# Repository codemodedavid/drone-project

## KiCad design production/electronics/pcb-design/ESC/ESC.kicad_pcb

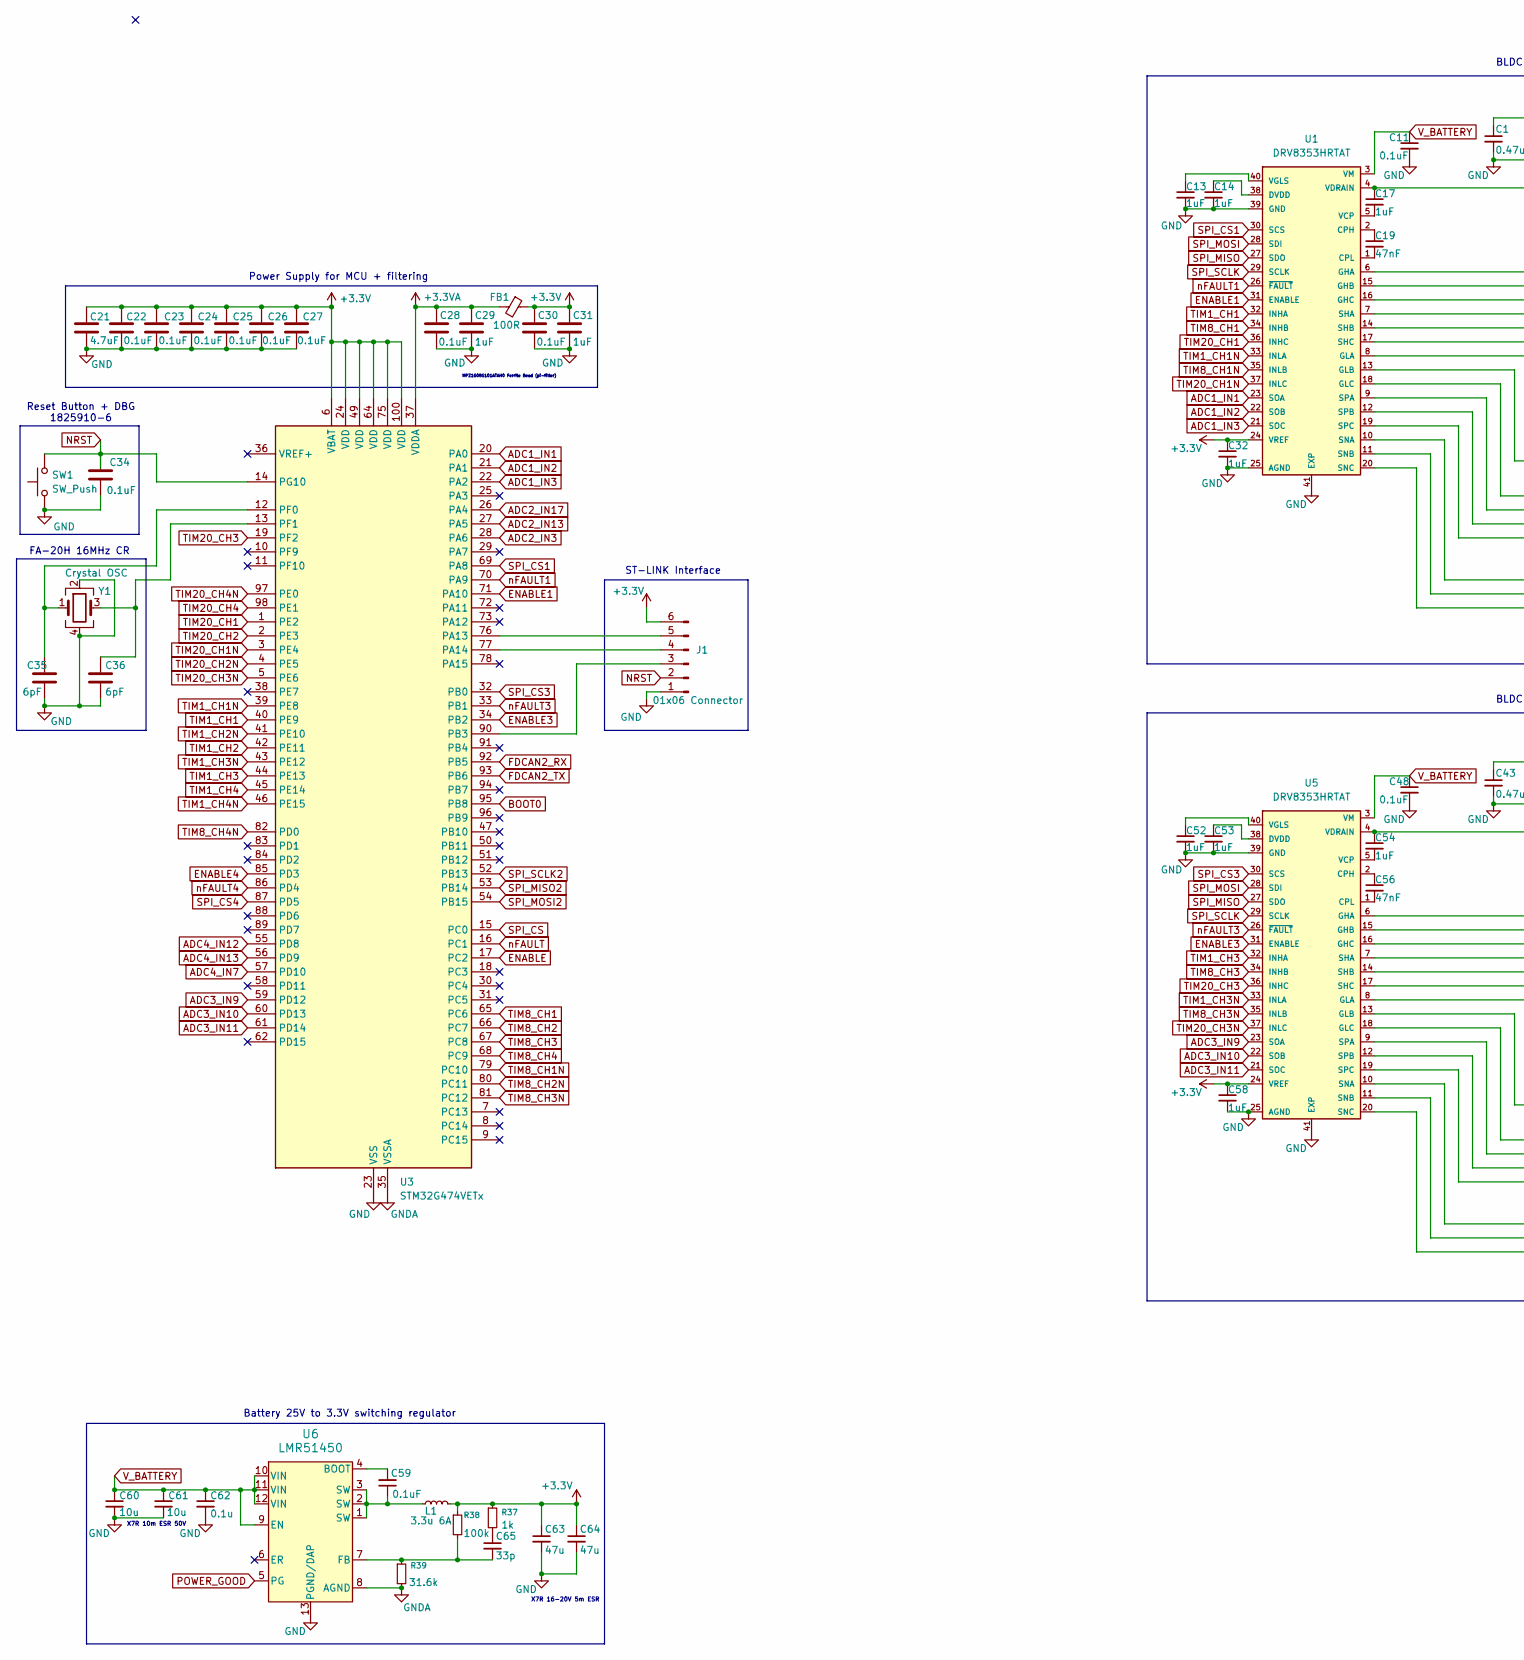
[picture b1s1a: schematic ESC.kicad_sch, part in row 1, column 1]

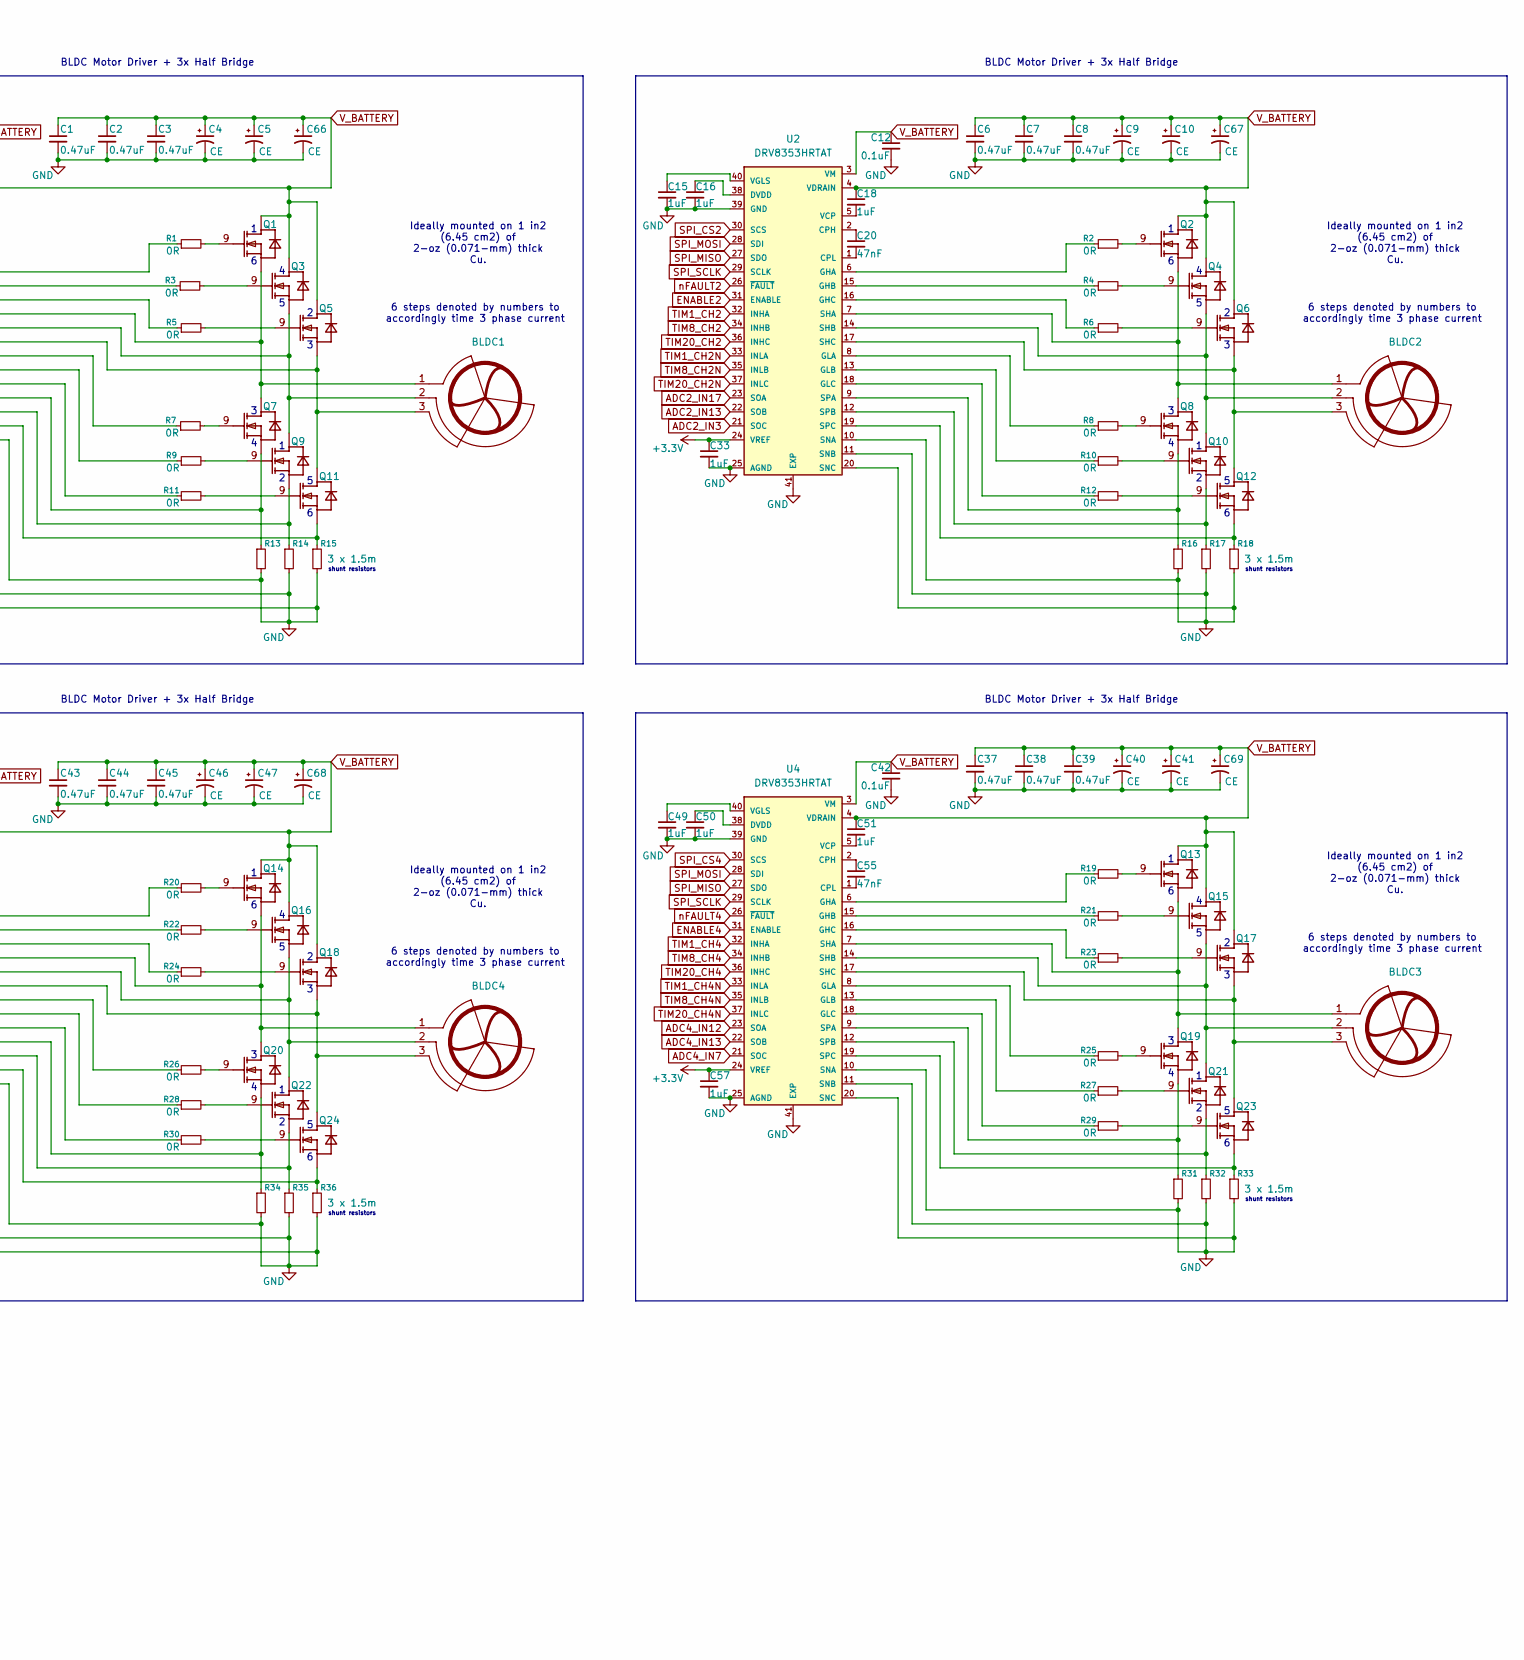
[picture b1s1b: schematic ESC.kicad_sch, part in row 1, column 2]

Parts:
BLDC1, BLDC2, BLDC3, BLDC4: (no value)
C1, C2, C3, C6, C7, C8, C37, C38, C39, C43, C44, C45: 0.47uF; C_0805_2012Metric_Pad1.18x1.45mm_HandSolder
C4, C5, C9, C10, C40, C41, C46, C47, C66, C67, C68, C69: CE; CAP_YX_12P5X25_RUB
C11, C12, C22, C23, C24, C25, C26, C27, C28, C30, C34, C42, C48, C59: 0.1uF; C_0603_1608Metric_Pad1.08x0.95mm_HandSolder
C13, C14, C15, C16, C17, C18, C29, C31, C32, C33, C49, C50, C51, C52, C53, C54, C57, C58: 1uF; C_0805_2012Metric_Pad1.18x1.45mm_HandSolder
C19, C20, C55, C56: 47nF; C_0603_1608Metric_Pad1.08x0.95mm_HandSolder
C21: 4.7uF; C_0805_2012Metric_Pad1.18x1.45mm_HandSolder
C35, C36: 6pF; C_0402_1005Metric_Pad0.74x0.62mm_HandSolder
C60, C61: 10u; C_1210_3225Metric_Pad1.33x2.70mm_HandSolder
C62: 0.1u; C_0603_1608Metric_Pad1.08x0.95mm_HandSolder
C63, C64: 47u; C_2220_5750Metric_Pad1.97x5.40mm_HandSolder
C65: 33p; C_0603_1608Metric_Pad1.08x0.95mm_HandSolder
FB1: 100R; IND_25_1806_FRT-M
J1: 01x06 Connector; PinHeader_1x06_P2.54mm_Vertical
L1: 3.3u 6A; IND_SRP6530A_BRN-M
Q1, Q2, Q3, Q4, Q5, Q6, Q7, Q8, Q9, Q10, Q11, Q12, Q13, Q14, Q15, Q16, Q17, Q18, Q19, Q20, Q21, Q22, Q23, Q24: IQDH88N06LM5CG; IFX-PG-TTFN-9-2-V-compat
R1, R2, R3, R4, R5, R6, R7, R8, R9, R10, R11, R12, R19, R20, R21, R22, R23, R24, R25, R26, R27, R28, R29, R30: 0R; R_0805_2012Metric_Pad1.20x1.40mm_HandSolder
R13, R14, R16, R17, R31, R32, R34, R35: R_Small; R_2512_6332Metric_Pad1.40x3.35mm_HandSolder
R15, R18, R33, R36: 3 x 1.5m; R_2512_6332Metric_Pad1.40x3.35mm_HandSolder
R37: 1k; R_0805_2012Metric_Pad1.20x1.40mm_HandSolder
R38: 100k; R_0805_2012Metric_Pad1.20x1.40mm_HandSolder
R39: 31.6k; R_0805_2012Metric_Pad1.20x1.40mm_HandSolder
SW1: SW_Push; SW_1825910-6-4
U1, U2, U4, U5: DRV8353HRTAT; QFN50P600X600X80-41N-vias; PARTREV A
U3: STM32G474VETx; LQFP100-14x14mm
U6: LMR51450; WSON12_DRR_TEX-M
Y1: Crystal OSC; XTAL4P_FA-20H_EPS

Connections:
+3.3V: C21.1, C22.1, C23.1, C24.1, C25.1, C26.1, C27.1, C30.1, C31.1, C32.1, C33.1, C57.1, C58.1, C63.1, C64.1, FB1.1, J1.6, L1.2, R37.1, R38.1, U1.24 (VREF), U2.24 (VREF), U3.6 (VBAT), U3.24 (VDD), U3.49 (VDD), U3.64 (VDD), U3.75 (VDD), U3.100 (VDD), U4.24 (VREF), U5.24 (VREF)
+3.3VA: C28.1, C29.1, FB1.2, U3.37 (VDDA)
ADC1_IN1: U1.23 (SOA), U3.20 (PA0)
ADC1_IN2: U1.22 (SOB), U3.21 (PA1)
ADC1_IN3: U1.21 (SOC), U3.22 (PA2)
ADC2_IN3: U2.21 (SOC), U3.28 (PA6)
ADC2_IN13: U2.22 (SOB), U3.27 (PA5)
ADC2_IN17: U2.23 (SOA), U3.26 (PA4)
ADC3_IN9: U3.59 (PD12), U5.23 (SOA)
ADC3_IN10: U3.60 (PD13), U5.22 (SOB)
ADC3_IN11: U3.61 (PD14), U5.21 (SOC)
ADC4_IN7: U3.57 (PD10), U4.21 (SOC)
ADC4_IN12: U3.55 (PD8), U4.23 (SOA)
ADC4_IN13: U3.56 (PD9), U4.22 (SOB)
BOOT0: U3.95 (PB8)
ENABLE: U3.17 (PC2)
ENABLE1: U1.31 (ENABLE), U3.71 (PA10)
ENABLE2: U2.31 (ENABLE)
ENABLE3: U3.34 (PB2), U5.31 (ENABLE)
ENABLE4: U3.85 (PD3), U4.31 (ENABLE)
FDCAN2_RX: U3.92 (PB5)
FDCAN2_TX: U3.93 (PB6)
GND: C1.2, C2.2, C3.2, C4.2, C5.2, C6.2, C7.2, C8.2, C9.2, C10.2, C11.2, C12.2, C13.2, C14.2, C15.2, C16.2, C21.2, C22.2, C23.2, C24.2, C25.2, C26.2, C27.2, C28.2, C29.2, C30.2, C31.2, C32.2, C33.2, C34.2, C35.2, C36.2, C37.2, C38.2, C39.2, C40.2, C41.2, C42.2, C43.2, C44.2, C45.2, C46.2, C47.2, C48.2, C49.2, C50.2, C52.2, C53.2, C57.2, C58.2, C60.2, C61.2, C62.2, C63.2, C64.2, C66.2, C67.2, C68.2, C69.2, J1.1, R13.2, R14.2, R15.2, R16.2, R17.2, R18.2, R31.2, R32.2, R33.2, R34.2, R35.2, R36.2, SW1.1, U1.10 (SNA), U1.11 (SNB), U1.20 (SNC), U1.25 (AGND), U1.39 (GND), U1.41 (EXP), U2.10 (SNA), U2.11 (SNB), U2.20 (SNC), U2.25 (AGND), U2.39 (GND), U2.41 (EXP), U3.23 (VSS), U3.48 (VSS), U3.63 (VSS), U3.74 (VSS), U3.99 (VSS), U4.10 (SNA), U4.11 (SNB), U4.20 (SNC), U4.25 (AGND), U4.39 (GND), U4.41 (EXP), U5.10 (SNA), U5.11 (SNB), U5.20 (SNC), U5.25 (AGND), U5.39 (GND), U5.41 (EXP), U6.13 (PGND/DAP), Y1.2, Y1.4
GNDA: R39.2, U3.35 (VSSA), U6.8 (AGND)
NRST: C34.1, J1.2, SW1.2, U3.14 (PG10)
unnamed: C59.1, L1.1, U6.1 (SW), U6.2 (SW), U6.3 (SW)
unnamed: C65.1, R37.2
unnamed: J1.3, U3.90 (PB3)
unnamed: J1.4, U3.77 (PA14)
unnamed: J1.5, U3.76 (PA13)
unnamed: Q1.9 (GATE), R1.2
unnamed: BLDC1.1, Q1.1 (SOURCE1), Q1.2 (SOURCE2), Q1.3 (SOURCE3), Q1.4 (SOURCE4), Q7.5 (DRAIN1), Q7.6 (DRAIN2), Q7.7 (DRAIN3), Q7.8 (DRAIN4), U1.7 (SHA)
unnamed: Q2.9 (GATE), R2.2
unnamed: BLDC2.1, Q2.1 (SOURCE1), Q2.2 (SOURCE2), Q2.3 (SOURCE3), Q2.4 (SOURCE4), Q8.5 (DRAIN1), Q8.6 (DRAIN2), Q8.7 (DRAIN3), Q8.8 (DRAIN4), U2.7 (SHA)
unnamed: Q3.9 (GATE), R3.2
unnamed: BLDC1.2, Q3.1 (SOURCE1), Q3.2 (SOURCE2), Q3.3 (SOURCE3), Q3.4 (SOURCE4), Q9.5 (DRAIN1), Q9.6 (DRAIN2), Q9.7 (DRAIN3), Q9.8 (DRAIN4), U1.14 (SHB)
unnamed: Q4.9 (GATE), R4.2
unnamed: Q5.9 (GATE), R5.2
unnamed: Q6.9 (GATE), R6.2
unnamed: Q7.9 (GATE), R7.2
unnamed: Q7.1 (SOURCE1), Q7.2 (SOURCE2), Q7.3 (SOURCE3), Q7.4 (SOURCE4), R13.1, U1.9 (SPA)
unnamed: Q8.9 (GATE), R8.2
unnamed: Q8.1 (SOURCE1), Q8.2 (SOURCE2), Q8.3 (SOURCE3), Q8.4 (SOURCE4), R16.1, U2.9 (SPA)
unnamed: Q9.9 (GATE), R9.2
unnamed: Q9.1 (SOURCE1), Q9.2 (SOURCE2), Q9.3 (SOURCE3), Q9.4 (SOURCE4), R14.1, U1.12 (SPB)
unnamed: BLDC2.2, Q4.1 (SOURCE1), Q4.2 (SOURCE2), Q4.3 (SOURCE3), Q4.4 (SOURCE4), Q10.5 (DRAIN1), Q10.6 (DRAIN2), Q10.7 (DRAIN3), Q10.8 (DRAIN4), U2.14 (SHB)
unnamed: Q10.9 (GATE), R10.2
unnamed: Q10.1 (SOURCE1), Q10.2 (SOURCE2), Q10.3 (SOURCE3), Q10.4 (SOURCE4), R17.1, U2.12 (SPB)
unnamed: BLDC1.3, Q5.1 (SOURCE1), Q5.2 (SOURCE2), Q5.3 (SOURCE3), Q5.4 (SOURCE4), Q11.5 (DRAIN1), Q11.6 (DRAIN2), Q11.7 (DRAIN3), Q11.8 (DRAIN4), U1.17 (SHC)
unnamed: Q11.9 (GATE), R11.2
unnamed: Q11.1 (SOURCE1), Q11.2 (SOURCE2), Q11.3 (SOURCE3), Q11.4 (SOURCE4), R15.1, U1.19 (SPC)
unnamed: BLDC2.3, Q6.1 (SOURCE1), Q6.2 (SOURCE2), Q6.3 (SOURCE3), Q6.4 (SOURCE4), Q12.5 (DRAIN1), Q12.6 (DRAIN2), Q12.7 (DRAIN3), Q12.8 (DRAIN4), U2.17 (SHC)
unnamed: Q12.9 (GATE), R12.2
unnamed: Q12.1 (SOURCE1), Q12.2 (SOURCE2), Q12.3 (SOURCE3), Q12.4 (SOURCE4), R18.1, U2.19 (SPC)
unnamed: Q13.9 (GATE), R19.2
unnamed: BLDC3.1, Q13.1 (SOURCE1), Q13.2 (SOURCE2), Q13.3 (SOURCE3), Q13.4 (SOURCE4), Q19.5 (DRAIN1), Q19.6 (DRAIN2), Q19.7 (DRAIN3), Q19.8 (DRAIN4), U4.7 (SHA)
unnamed: Q14.9 (GATE), R20.2
unnamed: BLDC4.1, Q14.1 (SOURCE1), Q14.2 (SOURCE2), Q14.3 (SOURCE3), Q14.4 (SOURCE4), Q20.5 (DRAIN1), Q20.6 (DRAIN2), Q20.7 (DRAIN3), Q20.8 (DRAIN4), U5.7 (SHA)
unnamed: Q15.9 (GATE), R21.2
unnamed: BLDC3.2, Q15.1 (SOURCE1), Q15.2 (SOURCE2), Q15.3 (SOURCE3), Q15.4 (SOURCE4), Q21.5 (DRAIN1), Q21.6 (DRAIN2), Q21.7 (DRAIN3), Q21.8 (DRAIN4), U4.14 (SHB)
unnamed: Q16.9 (GATE), R22.2
unnamed: BLDC4.2, Q16.1 (SOURCE1), Q16.2 (SOURCE2), Q16.3 (SOURCE3), Q16.4 (SOURCE4), Q22.5 (DRAIN1), Q22.6 (DRAIN2), Q22.7 (DRAIN3), Q22.8 (DRAIN4), U5.14 (SHB)
unnamed: Q17.9 (GATE), R23.2
unnamed: BLDC3.3, Q17.1 (SOURCE1), Q17.2 (SOURCE2), Q17.3 (SOURCE3), Q17.4 (SOURCE4), Q23.5 (DRAIN1), Q23.6 (DRAIN2), Q23.7 (DRAIN3), Q23.8 (DRAIN4), U4.17 (SHC)
unnamed: Q18.9 (GATE), R24.2
unnamed: BLDC4.3, Q18.1 (SOURCE1), Q18.2 (SOURCE2), Q18.3 (SOURCE3), Q18.4 (SOURCE4), Q24.5 (DRAIN1), Q24.6 (DRAIN2), Q24.7 (DRAIN3), Q24.8 (DRAIN4), U5.17 (SHC)
unnamed: Q19.9 (GATE), R25.2
unnamed: Q19.1 (SOURCE1), Q19.2 (SOURCE2), Q19.3 (SOURCE3), Q19.4 (SOURCE4), R31.1, U4.9 (SPA)
unnamed: Q20.9 (GATE), R26.2
unnamed: Q20.1 (SOURCE1), Q20.2 (SOURCE2), Q20.3 (SOURCE3), Q20.4 (SOURCE4), R34.1, U5.9 (SPA)
unnamed: Q21.9 (GATE), R27.2
unnamed: Q21.1 (SOURCE1), Q21.2 (SOURCE2), Q21.3 (SOURCE3), Q21.4 (SOURCE4), R32.1, U4.12 (SPB)
unnamed: Q22.9 (GATE), R28.2
unnamed: Q22.1 (SOURCE1), Q22.2 (SOURCE2), Q22.3 (SOURCE3), Q22.4 (SOURCE4), R35.1, U5.12 (SPB)
unnamed: Q23.9 (GATE), R29.2
unnamed: Q23.1 (SOURCE1), Q23.2 (SOURCE2), Q23.3 (SOURCE3), Q23.4 (SOURCE4), R33.1, U4.19 (SPC)
unnamed: Q24.9 (GATE), R30.2
unnamed: Q24.1 (SOURCE1), Q24.2 (SOURCE2), Q24.3 (SOURCE3), Q24.4 (SOURCE4), R36.1, U5.19 (SPC)
unnamed: C19.1, U1.2 (CPH)
unnamed: C19.2, U1.1 (CPL)
unnamed: C14.1, U1.38 (DVDD)
unnamed: R1.1, U1.6 (GHA)
unnamed: R3.1, U1.15 (GHB)
unnamed: R5.1, U1.16 (GHC)
unnamed: R7.1, U1.8 (GLA)
unnamed: R9.1, U1.13 (GLB)
unnamed: R11.1, U1.18 (GLC)
unnamed: C17.2, U1.5 (VCP)
unnamed: C13.1, U1.40 (VGLS)
unnamed: C20.1, U2.2 (CPH)
unnamed: C20.2, U2.1 (CPL)
unnamed: C16.1, U2.38 (DVDD)
unnamed: R2.1, U2.6 (GHA)
unnamed: R4.1, U2.15 (GHB)
unnamed: R6.1, U2.16 (GHC)
unnamed: R8.1, U2.8 (GLA)
unnamed: R10.1, U2.13 (GLB)
unnamed: R12.1, U2.18 (GLC)
unnamed: C18.2, U2.5 (VCP)
unnamed: C15.1, U2.40 (VGLS)
unnamed: C35.1, U3.12 (PF0), Y1.1
unnamed: C36.1, U3.13 (PF1), Y1.3
unnamed: C55.1, U4.2 (CPH)
unnamed: C55.2, U4.1 (CPL)
unnamed: C50.1, U4.38 (DVDD)
unnamed: R19.1, U4.6 (GHA)
unnamed: R21.1, U4.15 (GHB)
unnamed: R23.1, U4.16 (GHC)
unnamed: R25.1, U4.8 (GLA)
unnamed: R27.1, U4.13 (GLB)
unnamed: R29.1, U4.18 (GLC)
unnamed: C51.2, U4.5 (VCP)
unnamed: C49.1, U4.40 (VGLS)
unnamed: C56.1, U5.2 (CPH)
unnamed: C56.2, U5.1 (CPL)
unnamed: C53.1, U5.38 (DVDD)
unnamed: R20.1, U5.6 (GHA)
unnamed: R22.1, U5.15 (GHB)
unnamed: R24.1, U5.16 (GHC)
unnamed: R26.1, U5.8 (GLA)
unnamed: R28.1, U5.13 (GLB)
unnamed: R30.1, U5.18 (GLC)
unnamed: C54.2, U5.5 (VCP)
unnamed: C52.1, U5.40 (VGLS)
unnamed: C59.2, U6.4 (BOOT)
unnamed: C65.2, R38.2, R39.1, U6.7 (FB)
POWER_GOOD: U6.5 (PG)
SPI_CS: U3.15 (PC0)
SPI_CS1: U1.30 (SCS), U3.69 (PA8)
SPI_CS2: U2.30 (SCS)
SPI_CS3: U3.32 (PB0), U5.30 (SCS)
SPI_CS4: U3.87 (PD5), U4.30 (SCS)
SPI_MISO: U1.27 (SDO), U2.27 (SDO), U4.27 (SDO), U5.27 (SDO)
SPI_MISO2: U3.53 (PB14)
SPI_MOSI: U1.28 (SDI), U2.28 (SDI), U4.28 (SDI), U5.28 (SDI)
SPI_MOSI2: U3.54 (PB15)
SPI_SCLK: U1.29 (SCLK), U2.29 (SCLK), U4.29 (SCLK), U5.29 (SCLK)
SPI_SCLK2: U3.52 (PB13)
TIM1_CH1: U1.32 (INHA), U3.40 (PE9)
TIM1_CH1N: U1.33 (INLA), U3.39 (PE8)
TIM1_CH2: U2.32 (INHA), U3.42 (PE11)
TIM1_CH2N: U2.33 (INLA), U3.41 (PE10)
TIM1_CH3: U3.44 (PE13), U5.32 (INHA)
TIM1_CH3N: U3.43 (PE12), U5.33 (INLA)
TIM1_CH4: U3.45 (PE14), U4.32 (INHA)
TIM1_CH4N: U3.46 (PE15), U4.33 (INLA)
TIM8_CH1: U1.34 (INHB), U3.65 (PC6)
TIM8_CH1N: U1.35 (INLB), U3.79 (PC10)
TIM8_CH2: U2.34 (INHB), U3.66 (PC7)
TIM8_CH2N: U2.35 (INLB), U3.80 (PC11)
TIM8_CH3: U3.67 (PC8), U5.34 (INHB)
TIM8_CH3N: U3.81 (PC12), U5.35 (INLB)
TIM8_CH4: U3.68 (PC9), U4.34 (INHB)
TIM8_CH4N: U3.82 (PD0), U4.35 (INLB)
TIM20_CH1: U1.36 (INHC), U3.1 (PE2)
TIM20_CH1N: U1.37 (INLC), U3.3 (PE4)
TIM20_CH2: U2.36 (INHC), U3.2 (PE3)
TIM20_CH2N: U2.37 (INLC), U3.4 (PE5)
TIM20_CH3: U3.19 (PF2), U5.36 (INHC)
TIM20_CH3N: U3.5 (PE6), U5.37 (INLC)
TIM20_CH4: U3.98 (PE1), U4.36 (INHC)
TIM20_CH4N: U3.97 (PE0), U4.37 (INLC)
V_BATTERY: C1.1, C2.1, C3.1, C4.1, C5.1, C6.1, C7.1, C8.1, C9.1, C10.1, C11.1, C12.1, C17.1, C18.1, C37.1, C38.1, C39.1, C40.1, C41.1, C42.1, C43.1, C44.1, C45.1, C46.1, C47.1, C48.1, C51.1, C54.1, C60.1, C61.1, C62.1, C66.1, C67.1, C68.1, C69.1, Q1.5 (DRAIN1), Q1.6 (DRAIN2), Q1.7 (DRAIN3), Q1.8 (DRAIN4), Q2.5 (DRAIN1), Q2.6 (DRAIN2), Q2.7 (DRAIN3), Q2.8 (DRAIN4), Q3.5 (DRAIN1), Q3.6 (DRAIN2), Q3.7 (DRAIN3), Q3.8 (DRAIN4), Q4.5 (DRAIN1), Q4.6 (DRAIN2), Q4.7 (DRAIN3), Q4.8 (DRAIN4), Q5.5 (DRAIN1), Q5.6 (DRAIN2), Q5.7 (DRAIN3), Q5.8 (DRAIN4), Q6.5 (DRAIN1), Q6.6 (DRAIN2), Q6.7 (DRAIN3), Q6.8 (DRAIN4), Q13.5 (DRAIN1), Q13.6 (DRAIN2), Q13.7 (DRAIN3), Q13.8 (DRAIN4), Q14.5 (DRAIN1), Q14.6 (DRAIN2), Q14.7 (DRAIN3), Q14.8 (DRAIN4), Q15.5 (DRAIN1), Q15.6 (DRAIN2), Q15.7 (DRAIN3), Q15.8 (DRAIN4), Q16.5 (DRAIN1), Q16.6 (DRAIN2), Q16.7 (DRAIN3), Q16.8 (DRAIN4), Q17.5 (DRAIN1), Q17.6 (DRAIN2), Q17.7 (DRAIN3), Q17.8 (DRAIN4), Q18.5 (DRAIN1), Q18.6 (DRAIN2), Q18.7 (DRAIN3), Q18.8 (DRAIN4), U1.3 (VM), U1.4 (VDRAIN), U2.3 (VM), U2.4 (VDRAIN), U4.3 (VM), U4.4 (VDRAIN), U5.3 (VM), U5.4 (VDRAIN), U6.9 (EN), U6.10 (VIN), U6.11 (VIN), U6.12 (VIN)
nFAULT: U3.16 (PC1)
nFAULT1: U1.26 (~FAULT), U3.70 (PA9)
nFAULT2: U2.26 (~FAULT)
nFAULT3: U3.33 (PB1), U5.26 (~FAULT)
nFAULT4: U3.86 (PD4), U4.26 (~FAULT)

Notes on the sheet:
MPZ1608S101ATAH0 Ferrite Bead (pi-filter)
shunt resistors
BLDC Motor Driver + 3x Half Bridge
6 steps denoted by numbers to accordingly time 3 phase current
Ideally mounted on 1 in2 (6.45 cm2) of 2-oz (0.071-mm) thick Cu.
FA-20H 16MHz CR
Power Supply for MCU + filtering
X7R 10m ESR 50V
Battery 25V to 3.3V switching regulator
X7R 16-20V 5m ESR
ST-LINK Interface
Reset Button + DBG 1825910-6

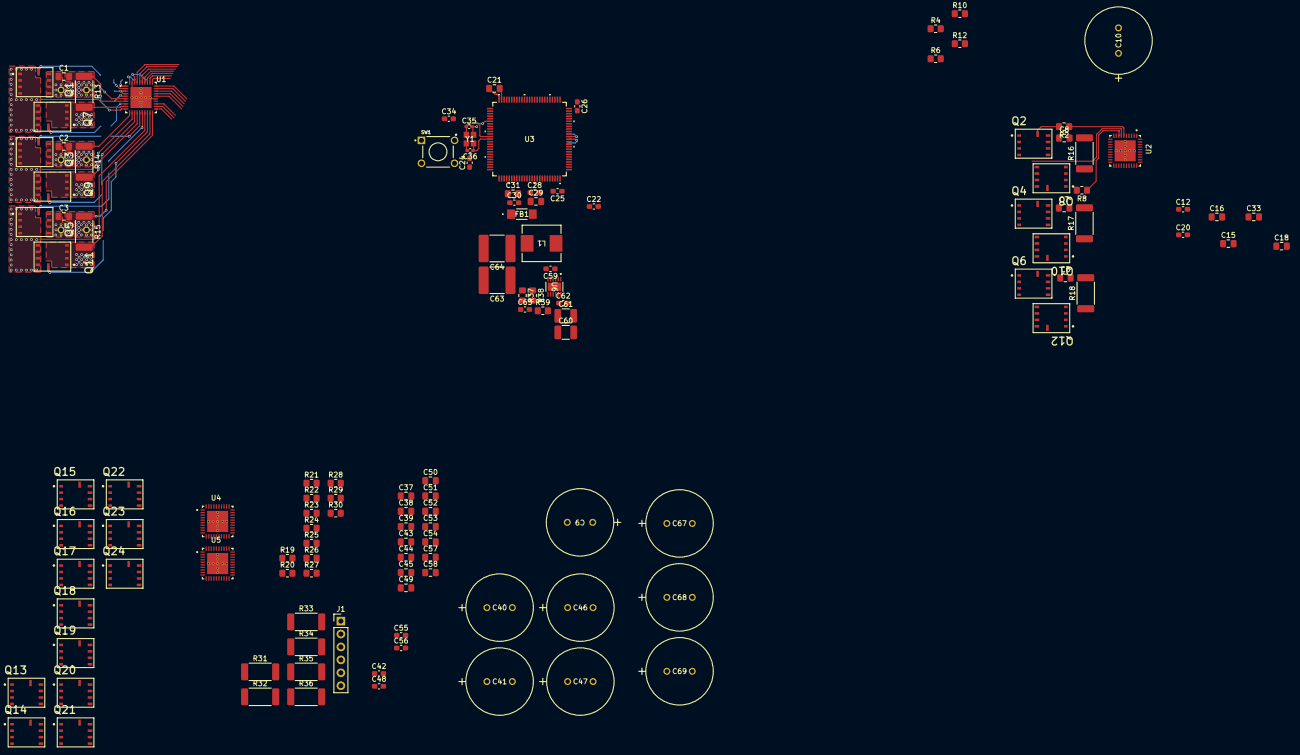
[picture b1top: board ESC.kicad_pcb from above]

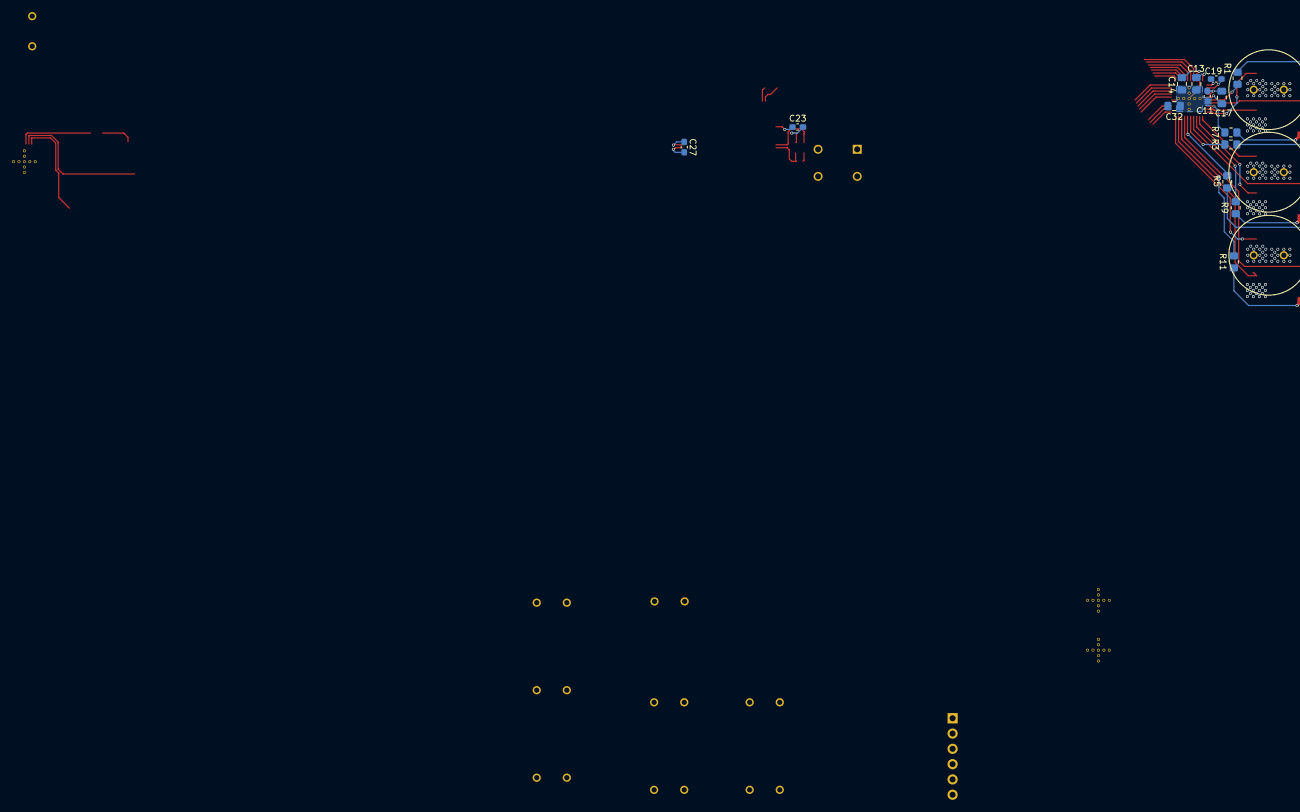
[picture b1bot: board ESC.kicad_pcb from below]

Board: 4 copper layers, 143 parts (17 on the bottom side), 155 nets.

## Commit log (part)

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2025-07-29 refactor(time_utils): Created time utilities library
2025-07-29 refactor(math_utils): Created math utilities library
2025-07-29 refactor(comm_utils): Created communication protocols utilities library
2025-07-29 refactor(callbacks): Created callback and interrupts managing library
2025-07-29 refactor(MPU6050): Created driver library for MPU6050 6-axis sensor (I2C)
    -initialization, settings, calibration
    -raw data acquisition and parsing via DMA
2025-07-29 refactor(BMP280): Created driver library for BMP280 Barometer (SPI)
    -initialization, settings
    -raw data acquisition and parsing via DMA
    -data calibration and processing functions
2025-07-29 refactor(pid_control): Created control library
    -PID control function
2025-07-29 refactor(main): Modularized main.c by extracting core functionality into separate libraries
    - Moved sensor drivers (MPU6050, BMP280) into dedicated libraries
    - Moved utilities (time, math, comms, callbacks) into dedicated libraries
    - Cleaned up main.c to improve readability and maintainability
    - Improved separation of concerns to facilitate future development
2025-12-25 Move existing KiCad FC & ESC files into repository; initial commit of components, footprints, schematics, and PCB layouts; organized project structure
2025-12-25 index on main: ce89418 Move existing KiCad FC & ESC files into repository; initial commit of components, footprints, schematics, and PCB layouts; organized project structure
2025-12-26 Work in progress: initial PCB layout commit; testing different layouts and routing for drivers + half-bridges
